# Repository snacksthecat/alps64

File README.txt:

ALPS 64 mini PCB
=====================
Primary goal is to provide support for some of the 14.5 unit key layouts.

Revisions
---------------
Rev.A   2018/05

Support Layouts
---------------
Apple Macintosh Portable (confirmed on a prototype pcb)
Apple M0116
Apple M0118
Apple M0330
NeXT Non-adb
Apple IIc (unsure)

To Do
---------------
Plates!

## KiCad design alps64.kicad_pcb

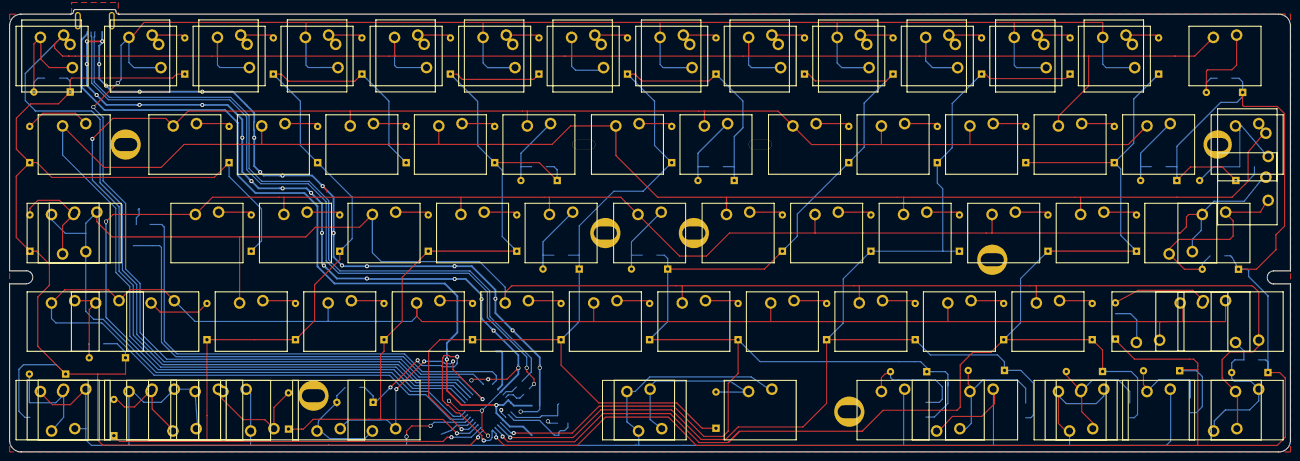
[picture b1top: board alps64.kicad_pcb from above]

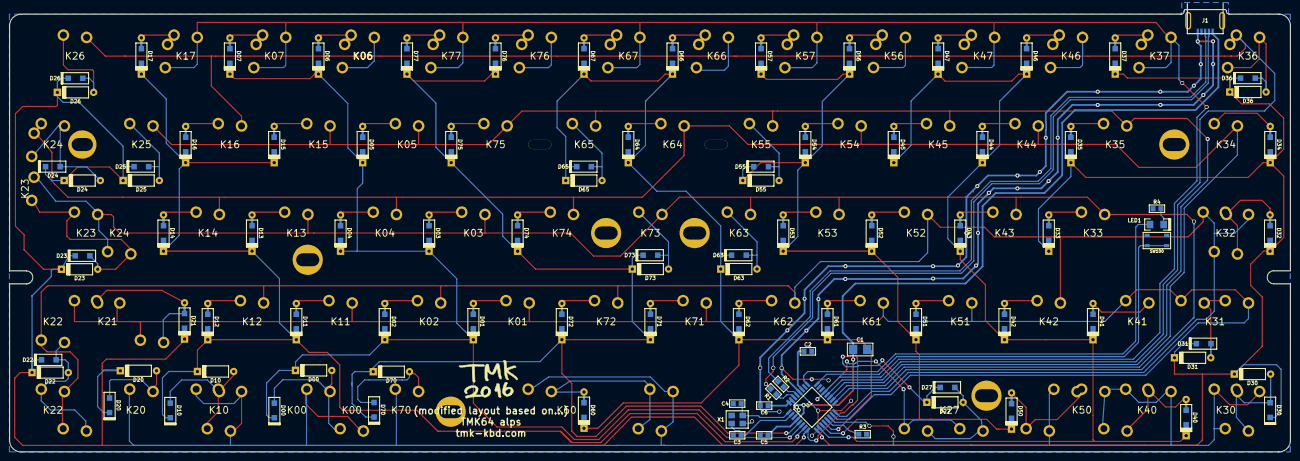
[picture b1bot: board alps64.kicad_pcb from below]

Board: 2 copper layers, 275.7 x 95.2 mm, 190 parts (96 on the bottom side), 93 nets.

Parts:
C1: 4.7u; C_3216
C2: 1u; C_1608
C3, C4: 10p; C_1608
C5, C6: 0.1u; C_1608
D00, D10, D20, D22, D23, D24, D25, D26, D27, D30#2, D31, D36, D55, D63, D65, D70, D73: D; D_SOD123_hand
D00#2, D10#2, D20#2, D22#2, D23#2, D24#2, D25#2, D26#2, D27#2, D30, D31#2, D36#2, D55#2, D63#2, D65#2, D70#2, D73#2: D; D_axial
D01, D02, D03, D04, D05, D06, D07, D11, D12, D13, D14, D15, D16, D17, D21, D32, D33, D34, D35, D37, D40, D41, D42, D43, D44, D45, D46, D47, D50, D51, D52, D53, D54, D56, D57, D60, D61, D62, D64, D66, D67, D71, D72, D74, D75, D76, D77: D; D_SOD123_axial
J1: USB_mini_micro_B; USB_miniB_hirose_5S8
K00, K00#2, K06#2, K10, K10_1, K20, K21, K24, K30, K31, K32, K36, K40, K41, K50, K50_2, K60, K60_1, K70: KEYSW; ALPS_SKCM_reverse_pad
K01, K02, K03, K04, K05, K06, K07, K10_2, K11, K12, K13, K14, K15, K16, K17, K21_1, K21_1#2, K22, K22#2, K23, K23_3, K25, K26, K27, K30_1, K30_1#2, K31_1, K32_1, K33, K34, K35, K37, K40_1, K40_2, K42, K43, K44, K45, K46, K47, K50_1, K51, K52, K53, K54, K55, K56, K57, K60_2, K61, K62, K63, K64, K65, K66, K67, K71, K72, K73, K74, K75, K76, K77: KEYSW; ALPS_SKCM
K32_2: ALPS_SKCM
LED1: LED; LED_3020_REFLOW
Poker_oval_hole: VAL**; Poker_oval_hole
Poker_oval_hole#2, Poker_oval_hole#3, Poker_oval_hole#4, Poker_oval_hole#5, Poker_oval_hole#6, Poker_oval_hole#7, Poker_oval_hole#8, Poker_oval_hole#9: VAL**; Poker_oval_hole
Poker_side_edge_long: VAL**; Poker_side_edge_long
Poker_side_edge_long#2: VAL**; Poker_side_edge_long
R1, R2: 22; R_1608
R3: 1K; R_1608
R4: 1.5K; R_1608
SW100: SW_PUSH; SW_ALPS_SKRP
U1: 32U2; QFP32_reflow
X1: CRYSTAL; FA-238

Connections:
+5V: C1.1, C5.1, C6.1, J1.1, U1.4, U1.31, U1.32
/D+: J1.3, R2.1
/D+R: R2.2, U1.29
/D-: J1.2, R1.1
/D-R: R1.2, U1.30
/matrix/col0: K00.1, K00#2.1, K10.1, K10_1.1, K10_2.1, K20.1, K30.1, K30_1.1, K30_1#2.1, K40.1, K40_1.1, K40_2.1, K50.1, K50_1.1, K50_2.1, K60.1, K60_1.1, K60_2.1, K70.1, U1.14
/matrix/col1: K01.1, K11.1, K21.1, K21_1.1, K21_1#2.1, K31.1, K31_1.1, K41.1, K51.1, K61.1, K71.1, U1.15
/matrix/col2: K02.1, K12.1, K22.1, K22#2.1, K32.1, K32_1.1, K32_2.1, K42.1, K52.1, K62.1, K72.1, U1.16
/matrix/col3: K03.1, K13.1, K23.1, K23_3.1, K33.1, K43.1, K53.1, K63.1, K73.1, U1.17
/matrix/col4: K04.1, K14.1, K24.1, K34.1, K44.1, K54.1, K64.1, K74.1, U1.18
/matrix/col5: K05.1, K15.1, K25.1, K35.1, K45.1, K55.1, K65.1, K75.1, U1.19
/matrix/col6: K06.1, K06#2.1, K16.1, K26.1, K36.1, K46.1, K56.1, K66.1, K76.1, U1.20
/matrix/col7: K07.1, K17.1, K27.1, K37.1, K47.1, K57.1, K67.1, K77.1, U1.21
/matrix/row0: D00.2, D00#2.2, D01.2, D02.2, D03.2, D04.2, D05.2, D06.2, D07.2, U1.6
/matrix/row1: D10.2, D10#2.2, D11.2, D12.2, D13.2, D14.2, D15.2, D16.2, D17.2, U1.7
/matrix/row2: D20.2, D20#2.2, D21.2, D22.2, D22#2.2, D23.2, D23#2.2, D24.2, D24#2.2, D25.2, D25#2.2, D26.2, D26#2.2, D27.2, D27#2.2, U1.8
/matrix/row3: D30.2, D30#2.2, D31.2, D31#2.2, D32.2, D33.2, D34.2, D35.2, D36.2, D36#2.2, D37.2, U1.9
/matrix/row4: D40.2, D41.2, D42.2, D43.2, D44.2, D45.2, D46.2, D47.2, U1.10
/matrix/row5: D50.2, D51.2, D52.2, D53.2, D54.2, D55.2, D55#2.2, D56.2, D57.2, U1.11
/matrix/row6: D60.2, D61.2, D62.2, D63.2, D63#2.2, D64.2, D65.2, D65#2.2, D66.2, D67.2, U1.12
/matrix/row7: D70.2, D70#2.2, D71.2, D72.2, D73.2, D73#2.2, D74.2, D75.2, D76.2, D77.2, U1.5
GND: C1.2, C2.2, C3.2, C4.2, C5.2, C6.2, J1.5, J1.6, R3.2, R4.2, SW100.2, U1.3, U1.28, X1.3
unnamed: C2.1, U1.27
unnamed: C3.1, U1.2, X1.2
unnamed: C4.1, U1.1, X1.1
unnamed: D00.1, D00#2.1, K00.2, K00#2.2
unnamed: D01.1, K01.2
unnamed: D02.1, K02.2
unnamed: D03.1, K03.2
unnamed: D04.1, K04.2
unnamed: D05.1, K05.2
unnamed: D06.1, K06.2, K06#2.2
unnamed: D07.1, K07.2
unnamed: D10.1, D10#2.1, K10.2, K10_1.2, K10_2.2
unnamed: D11.1, K11.2
unnamed: D12.1, K12.2
unnamed: D13.1, K13.2
unnamed: D14.1, K14.2
unnamed: D15.1, K15.2
unnamed: D16.1, K16.2
unnamed: D17.1, K17.2
unnamed: D20.1, D20#2.1, K20.2
unnamed: D21.1, K21.2, K21_1.2, K21_1#2.2
unnamed: D22.1, D22#2.1, K22.2, K22#2.2
unnamed: D23.1, D23#2.1, K23.2, K23_3.2
unnamed: D24.1, D24#2.1, K24.2
unnamed: D25.1, D25#2.1, K25.2
unnamed: D26.1, D26#2.1, K26.2
unnamed: D27.1, D27#2.1, K27.2
unnamed: D30.1, D30#2.1, K30.2, K30_1.2, K30_1#2.2
unnamed: D31.1, D31#2.1, K31.2, K31_1.2
unnamed: D32.1, K32.2, K32_1.2, K32_2.2
unnamed: D33.1, K33.2
unnamed: D34.1, K34.2
unnamed: D35.1, K35.2
unnamed: D36.1, D36#2.1, K36.2
unnamed: D37.1, K37.2
unnamed: D40.1, K40.2, K40_1.2, K40_2.2
unnamed: D41.1, K41.2
unnamed: D42.1, K42.2
unnamed: D43.1, K43.2
unnamed: D44.1, K44.2
unnamed: D45.1, K45.2
unnamed: D46.1, K46.2
unnamed: D47.1, K47.2
unnamed: D50.1, K50.2, K50_1.2, K50_2.2
unnamed: D51.1, K51.2
unnamed: D52.1, K52.2
unnamed: D53.1, K53.2
unnamed: D54.1, K54.2
unnamed: D55.1, D55#2.1, K55.2
unnamed: D56.1, K56.2
unnamed: D57.1, K57.2
unnamed: D60.1, K60.2, K60_1.2, K60_2.2
unnamed: D61.1, K61.2
unnamed: D62.1, K62.2
unnamed: D63.1, D63#2.1, K63.2
unnamed: D64.1, K64.2
unnamed: D65.1, D65#2.1, K65.2
unnamed: D66.1, K66.2
unnamed: D67.1, K67.2
unnamed: D70.1, D70#2.1, K70.2
unnamed: D71.1, K71.2
unnamed: D72.1, K72.2
unnamed: D73.1, D73#2.1, K73.2
unnamed: D74.1, K74.2
unnamed: D75.1, K75.2
unnamed: D76.1, K76.2
unnamed: D77.1, K77.2
unnamed: LED1.2, U1.25
unnamed: LED1.1, R4.1
unnamed: R3.1, U1.13
unnamed: SW100.1, U1.24
